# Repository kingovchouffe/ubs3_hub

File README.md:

# ubs3_hub
ch634 based USB3 5Gbps 4 ports hub

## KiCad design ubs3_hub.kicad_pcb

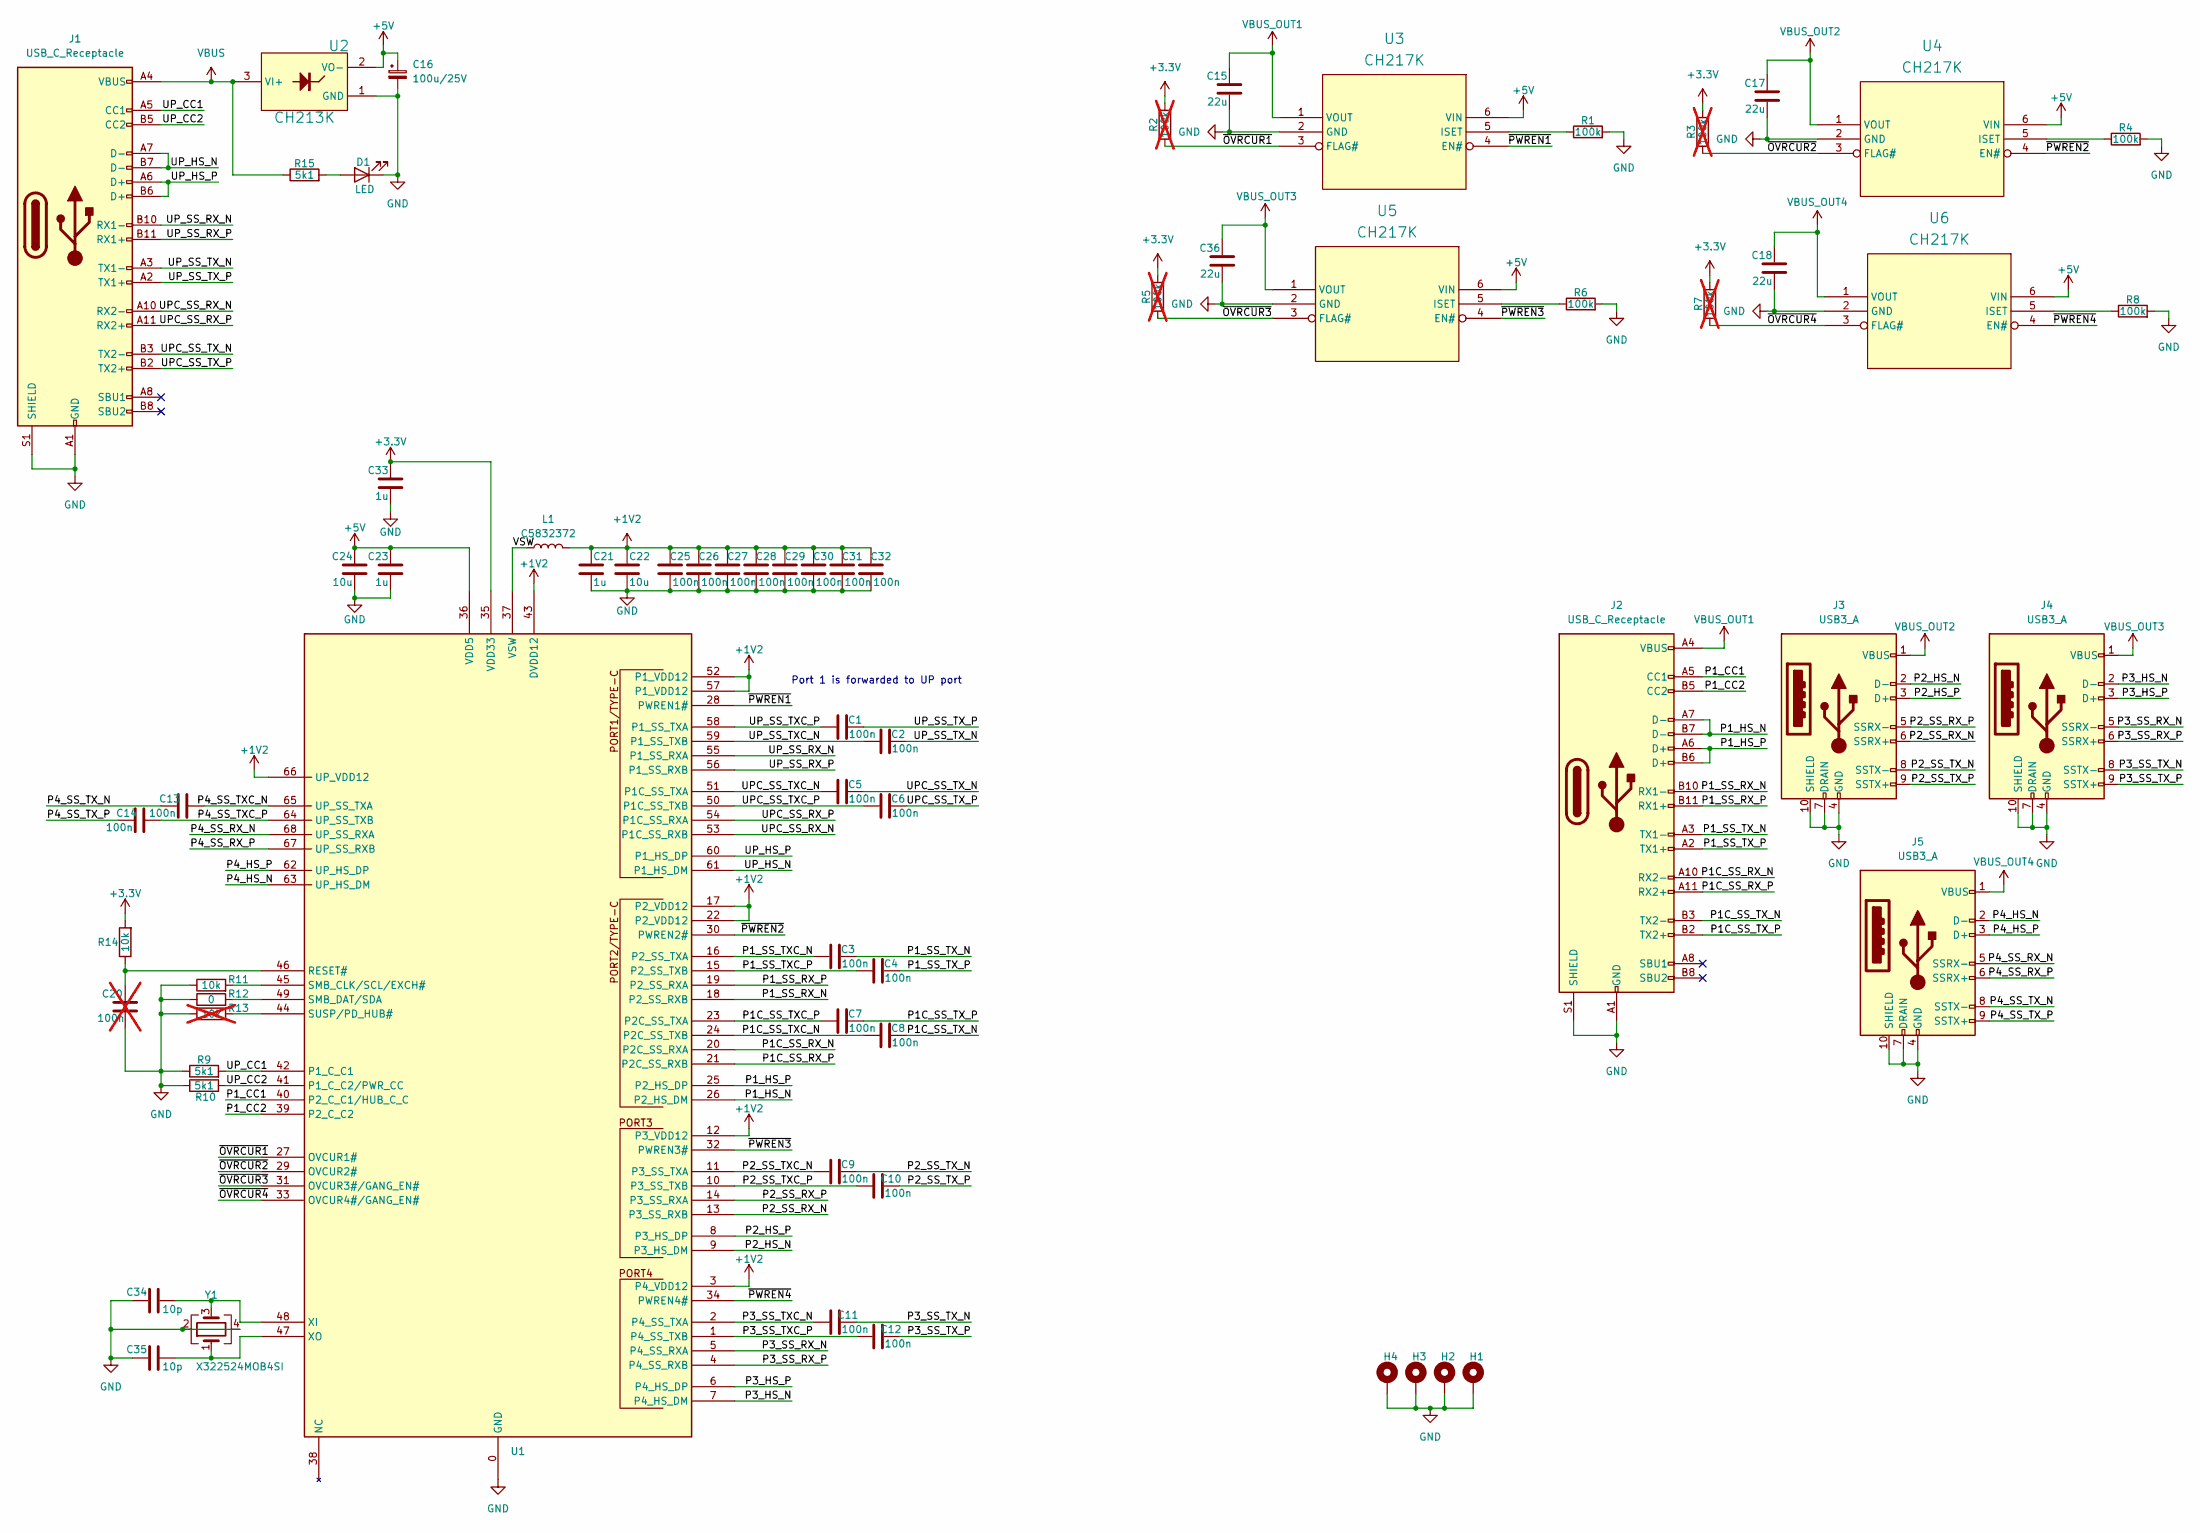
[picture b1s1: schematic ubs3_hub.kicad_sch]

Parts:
C1, C2, C3, C4, C5, C6, C7, C8, C9, C10, C11, C12, C13, C14, C25, C26, C27, C28, C29, C30, C31, C32: 100n; C_0402_1005Metric
C15, C17, C18, C36: 22u; C_0805_2012Metric
C16: 100u/25V; CP_Elec_6.3x7.7
C20: 100n; C_0603_1608Metric; not fitted
C21, C23, C33: 1u; C_0805_2012Metric
C22, C24: 10u; C_0805_2012Metric
C34, C35: 10p; C_0603_1608Metric
D1: LED; LED_0805_2012Metric
H1, H2, H3, H4: MountingHole_Pad; MountingHole_3.2mm_M3_Pad_Via
J1, J2: USB_C_Receptacle; USB_C_Receptacle_Amphenol_12401610E4-2A
J3, J4, J5: USB3_A; USB3_A_Molex_48393-001
L1: C5832372; L_Changjiang_FTC201610D
R1, R4, R6, R8: 100k; R_0603_1608Metric
R2, R3, R5, R7: 100k; R_0603_1608Metric; not fitted
R9, R10, R15: 5k1; R_0603_1608Metric
R11, R14: 10k; R_0603_1608Metric
R12: 0; R_0603_1608Metric
R13: 10k; R_0603_1608Metric; not fitted
U1: QFN68_8X8
U2: CH213K; SOT-23-3
U3, U4, U5, U6: CH217K; SOT-23-6
Y1: X322524MOB4SI; Crystal_SMD_3225-4Pin_3.2x2.5mm

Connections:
+1V2: C21.1, C22.1, C25.2, C26.2, C27.2, C28.2, C29.2, C30.2, C31.2, C32.2, L1.2, U1.3 (P4_VDD12), U1.12 (P3_VDD12), U1.17 (P2_VDD12), U1.22 (P2_VDD12), U1.43 (DVDD12), U1.52 (P1_VDD12), U1.57 (P1_VDD12), U1.66 (UP_VDD12)
+3.3V: C33.1, R2.2, R3.2, R5.2, R7.2, R14.2, U1.35 (VDD33)
+5V: C16.1, C23.1, C24.1, U1.36 (VDD5), U2.2 (VO-), U3.6 (VIN), U4.6 (VIN), U5.6 (VIN), U6.6 (VIN)
/P1C_SS_RX_N: J2.A10 (RX2-), U1.20 (P2C_SS_RXA)
/P1C_SS_RX_P: J2.A11 (RX2+), U1.21 (P2C_SS_RXB)
/P1C_SS_TXC_N: C8.1, U1.24 (P2C_SS_TXB)
/P1C_SS_TXC_P: C7.1, U1.23 (P2C_SS_TXA)
/P1C_SS_TX_N: C8.2, J2.B3 (TX2-)
/P1C_SS_TX_P: C7.2, J2.B2 (TX2+)
/P1_CC1: J2.A5 (CC1), U1.40 (P2_C_C1/HUB_C_C)
/P1_CC2: J2.B5 (CC2), U1.39 (P2_C_C2)
/P1_HS_N: J2.A7 (D-), J2.B7 (D-), U1.26 (P2_HS_DM)
/P1_HS_P: J2.A6 (D+), J2.B6 (D+), U1.25 (P2_HS_DP)
/P1_SS_RX_N: J2.B10 (RX1-), U1.18 (P2_SS_RXB)
/P1_SS_RX_P: J2.B11 (RX1+), U1.19 (P2_SS_RXA)
/P1_SS_TXC_N: C3.1, U1.16 (P2_SS_TXA)
/P1_SS_TXC_P: C4.1, U1.15 (P2_SS_TXB)
/P1_SS_TX_N: C3.2, J2.A3 (TX1-)
/P1_SS_TX_P: C4.2, J2.A2 (TX1+)
/P2_HS_N: J3.2 (D-), U1.9 (P3_HS_DM)
/P2_HS_P: J3.3 (D+), U1.8 (P3_HS_DP)
/P2_SS_RX_N: J3.6 (SSRX+), U1.13 (P3_SS_RXB)
/P2_SS_RX_P: J3.5 (SSRX-), U1.14 (P3_SS_RXA)
/P2_SS_TXC_N: C9.1, U1.11 (P3_SS_TXA)
/P2_SS_TXC_P: C10.1, U1.10 (P3_SS_TXB)
/P2_SS_TX_N: C9.2, J3.8 (SSTX-)
/P2_SS_TX_P: C10.2, J3.9 (SSTX+)
/P3_HS_N: J4.2 (D-), U1.7 (P4_HS_DM)
/P3_HS_P: J4.3 (D+), U1.6 (P4_HS_DP)
/P3_SS_RX_N: J4.5 (SSRX-), U1.5 (P4_SS_RXA)
/P3_SS_RX_P: J4.6 (SSRX+), U1.4 (P4_SS_RXB)
/P3_SS_TXC_N: C11.1, U1.2 (P4_SS_TXA)
/P3_SS_TXC_P: C12.1, U1.1 (P4_SS_TXB)
/P3_SS_TX_N: C11.2, J4.8 (SSTX-)
/P3_SS_TX_P: C12.2, J4.9 (SSTX+)
/P4_HS_N: J5.2 (D-), U1.63 (UP_HS_DM)
/P4_HS_P: J5.3 (D+), U1.62 (UP_HS_DP)
/P4_SS_RX_N: J5.5 (SSRX-), U1.68 (UP_SS_RXA)
/P4_SS_RX_P: J5.6 (SSRX+), U1.67 (UP_SS_RXB)
/P4_SS_TXC_N: C13.1, U1.65 (UP_SS_TXA)
/P4_SS_TXC_P: C14.1, U1.64 (UP_SS_TXB)
/P4_SS_TX_N: C13.2, J5.8 (SSTX-)
/P4_SS_TX_P: C14.2, J5.9 (SSTX+)
/UPC_SS_RX_N: J1.A10 (RX2-), U1.53 (P1C_SS_RXB)
/UPC_SS_RX_P: J1.A11 (RX2+), U1.54 (P1C_SS_RXA)
/UPC_SS_TXC_N: C5.1, U1.51 (P1C_SS_TXA)
/UPC_SS_TXC_P: C6.1, U1.50 (P1C_SS_TXB)
/UPC_SS_TX_N: C5.2, J1.B3 (TX2-)
/UPC_SS_TX_P: C6.2, J1.B2 (TX2+)
/UP_CC1: J1.A5 (CC1), R9.2, U1.42 (P1_C_C1)
/UP_CC2: J1.B5 (CC2), R10.2, U1.41 (P1_C_C2/PWR_CC)
/UP_HS_N: J1.A7 (D-), J1.B7 (D-), U1.61 (P1_HS_DM)
/UP_HS_P: J1.A6 (D+), J1.B6 (D+), U1.60 (P1_HS_DP)
/UP_SS_RX_N: J1.B10 (RX1-), U1.55 (P1_SS_RXA)
/UP_SS_RX_P: J1.B11 (RX1+), U1.56 (P1_SS_RXB)
/UP_SS_TXC_N: C2.1, U1.59 (P1_SS_TXB)
/UP_SS_TXC_P: C1.1, U1.58 (P1_SS_TXA)
/UP_SS_TX_N: C2.2, J1.A3 (TX1-)
/UP_SS_TX_P: C1.2, J1.A2 (TX1+)
/VSW: L1.1, U1.37 (VSW)
/~OVRCUR1: R2.1, U1.27 (OVCUR1#), U3.3 (FLAG#)
/~OVRCUR2: R3.1, U1.29 (OVCUR2#), U4.3 (FLAG#)
/~OVRCUR3: R5.1, U1.31 (OVCUR3#/GANG_EN#), U5.3 (FLAG#)
/~OVRCUR4: R7.1, U1.33 (OVCUR4#/GANG_EN#), U6.3 (FLAG#)
/~PWREN1: U1.28 (PWREN1#), U3.4 (EN#)
/~PWREN2: U1.30 (PWREN2#), U4.4 (EN#)
/~PWREN3: U1.32 (PWREN3#), U5.4 (EN#)
/~PWREN4: U1.34 (PWREN4#), U6.4 (EN#)
GND: C15.2, C16.2, C17.2, C18.2, C20.2, C21.2, C22.2, C23.2, C24.2, C25.1, C26.1, C27.1, C28.1, C29.1, C30.1, C31.1, C32.1, C33.2, C34.1, C35.1, C36.2, D1.1 (K), H1.1, H2.1, H3.1, H4.1, J1.A1 (GND), J1.A12 (GND), J1.B1 (GND), J1.B12 (GND), J1.S1 (SHIELD), J2.A1 (GND), J2.A12 (GND), J2.B1 (GND), J2.B12 (GND), J2.S1 (SHIELD), J3.4 (GND), J3.7 (DRAIN), J3.10 (SHIELD), J4.4 (GND), J4.7 (DRAIN), J4.10 (SHIELD), J5.4 (GND), J5.7 (DRAIN), J5.10 (SHIELD), R1.2, R4.2, R6.2, R8.2, R9.1, R10.1, R11.1, R12.1, R13.1, U1.0 (GND), U2.1 (GND), U3.2 (GND), U4.2 (GND), U5.2 (GND), U6.2 (GND), Y1.2, Y1.4
unnamed: D1.2 (A), R15.2
unnamed: C20.1, R14.1, U1.46 (RESET#)
unnamed: R11.2, U1.45 (SMB_CLK/SCL/EXCH#)
unnamed: R12.2, U1.49 (SMB_DAT/SDA)
unnamed: R13.2, U1.44 (SUSP/PD_HUB#)
unnamed: C34.2, U1.48 (XI), Y1.3
unnamed: C35.2, U1.47 (XO), Y1.1
unnamed: R1.1, U3.5 (ISET)
unnamed: R4.1, U4.5 (ISET)
unnamed: R6.1, U5.5 (ISET)
unnamed: R8.1, U6.5 (ISET)
VBUS: J1.A4 (VBUS), J1.A9 (VBUS), J1.B4 (VBUS), J1.B9 (VBUS), R15.1, U2.3 (VI+)
VBUS_OUT1: C15.1, J2.A4 (VBUS), J2.A9 (VBUS), J2.B4 (VBUS), J2.B9 (VBUS), U3.1 (VOUT)
VBUS_OUT2: C17.1, J3.1 (VBUS), U4.1 (VOUT)
VBUS_OUT3: C36.1, J4.1 (VBUS), U5.1 (VOUT)
VBUS_OUT4: C18.1, J5.1 (VBUS), U6.1 (VOUT)

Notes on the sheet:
Port 1 is forwarded to UP port

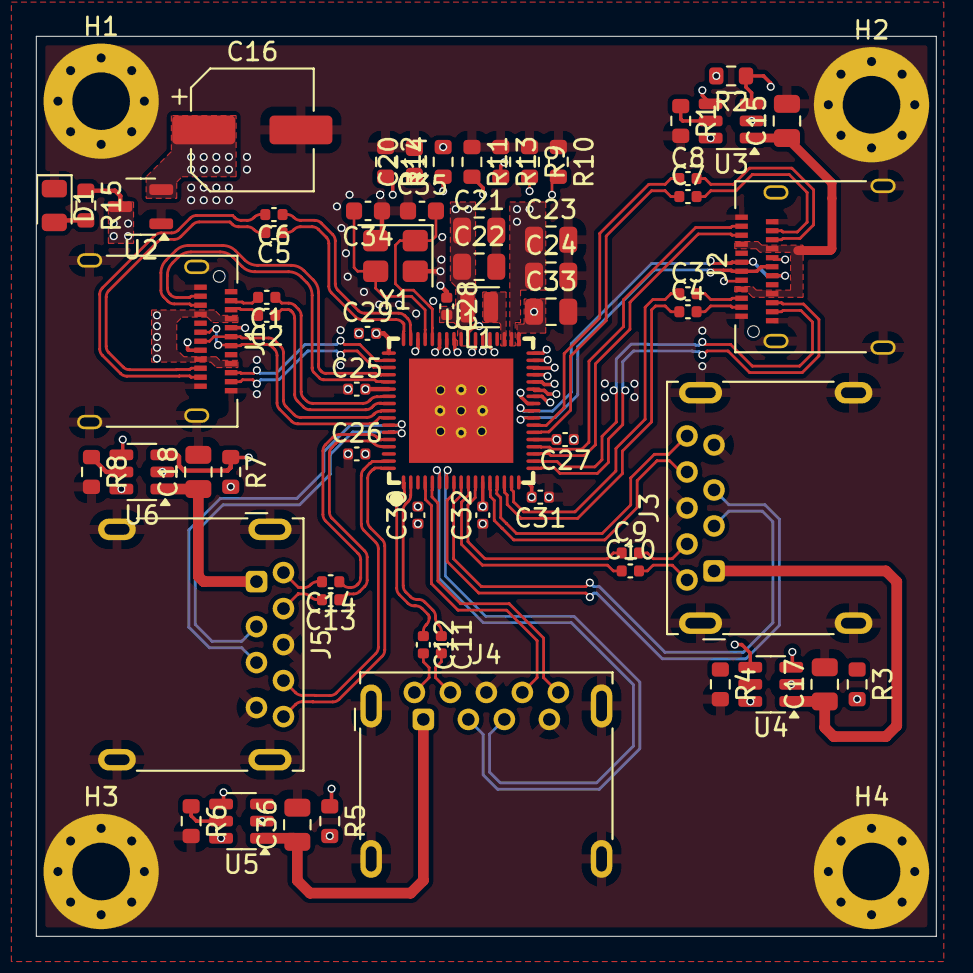
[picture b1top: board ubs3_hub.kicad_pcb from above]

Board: 6 copper layers, 50.0 x 50.0 mm, 68 parts (0 on the bottom side), 85 nets.

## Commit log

2025-10-18 placement finished, power layout ok
2025-10-19 Layout in progress
2025-10-21 updated layout
